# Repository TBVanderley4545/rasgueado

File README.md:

# Rasgueado

## Overview

Rasgueado - A strumming technique associated with flamenco music. Also, replacement controllers for Kinesis Advantage 2 boards.

This project was inspired by work from the [KinT project](https://github.com/kinx-project/kint) and the [Pillz Mod project](https://github.com/dcpedit/pillzmod).

The goal of this project was really simple, I wanted Nice!Nanos and ZMK in my Kinesis Advantage 2 boards. I wanted to make this PCB as simple as possible, so it is really barebones - no LEDs, no plans for batteries, just plain simple ZMK goodness. If I want to use my boards unplugged from my computer, I plug them into an external battery bank. I like this approach better because of super long battery life, easier modularity, and not needing to source tiny batteries.

In addition to the main controller, there are replacement thumb PCBs as well as plate files. Why? I wanted hotswap thumb clusters and carbon fiber plates. So, voila there are now hotswap thumb cluster PCBs and thumb plates that can be made in carbon fiber or whatever other material you please. Nice.

## Usage

You can find the zipped gerbers (for the pcb) and dxf file (for the plates) to send off for manufacturing or clone this repo and make whatever changes you want.

If you are working on the Kicad files, you will need to setup your Kicad to reference the following libraries:

- [ai03-2725 MX_V2 library](https://github.com/ai03-2725/MX_V2)
- [ScottoKicad library](https://github.com/joe-scotto/scottokeebs/tree/main/Extras/ScottoKicad)

## Parts lists

These parts lists are just based off of what I used and are here to help point you in the right direction. Feel free to buy from different places.

### Main Controller

| Part                                             | Qty | Notes                                                                                                                                                                                                                                                                                                                                                                                                                                                                          |
| ------------------------------------------------ | --- | ------------------------------------------------------------------------------------------------------------------------------------------------------------------------------------------------------------------------------------------------------------------------------------------------------------------------------------------------------------------------------------------------------------------------------------------------------------------------------ |
| Nice!Nano V2                                     | 1   | The MCU. The brains behind the board. [Link](https://typeractive.xyz/products/nice-nano?_pos=1&_sid=3e0c6f7de&_ss=r)                                                                                                                                                                                                                                                                                                                                                           |
| EZ-Solder Machine Sockets and Headers (optional) | 1   | These are optional, but they make socketing the Nice!Nano a breeze. I won't build without them personally. Your call though. [Link](https://typeractive.xyz/products/ez-machine-sockets-and-headers?_pos=3&_sid=3e0c6f7de&_ss=r)                                                                                                                                                                                                                                               |
| Molex 39-53-2135                                 | 6   | Connector for flat cables of other boards to plug into main board. [Link](https://www.digikey.com/en/products/detail/molex/0039532135/3160262)                                                                                                                                                                                                                                                                                                                                 |
| SN74HC595N Shift Register                        | 1   | Shift registers are cool. They make not enough GPIO pins into more than enough GPIO pins. Praise be to the shift registers. [Link](https://www.amazon.com/dp/B0CBKJXP13?ref_=ppx_hzsearch_conn_dt_b_fed_asin_title_1&th=1)                                                                                                                                                                                                                                                     |
| Shift Register Sockets                           | 1   | Sockets your shift register. Sweeeeeet. [Link](https://www.amazon.com/dp/B00SWO3U1C?ref_=ppx_hzsearch_conn_dt_b_fed_asin_title_2)                                                                                                                                                                                                                                                                                                                                              |
| USB C panel jack (optional)                      | 1   | This gives you a place to attach and detach USB C cables to the keyboard. Is this optional? Yes. It is indeed optional if you want to directly attach a USB C cable to your MCU and run the risk of damaging it and deal with never swapping out the cable easily. It is indeed optional. It's just a bad option not to. You live life on the edge. Installing this does require dremelling some material from your case though. [Link](https://www.adafruit.com/product/4218) |

### Thumbs

| Part                        | Qty | Notes                                                                                                                                                                                                                                                                                                               |
| --------------------------- | --- | ------------------------------------------------------------------------------------------------------------------------------------------------------------------------------------------------------------------------------------------------------------------------------------------------------------------- |
| Molex 39-53-2135            | 2   | Connector for flat cables of other boards to plug into main board. [Link](https://www.digikey.com/en/products/detail/molex/0039532135/3160262)                                                                                                                                                                      |
| Flat flex cables (optional) | 2   | These are just replacement flat cables. They were thinner and easier to work with than the stock ones. You can probably just reuse the stock cables, but I wanted to have extras. So... I did the sensible thing. I bought 30 "backups" [Link](https://www.digikey.com/en/products/detail/molex/0151680815/4143332) |
| 1N4148W SOD-123 diodes      | 12  | Diodes. They let signal go one way, but not the other. Without these there is only chaos. [Link](https://typeractive.xyz/products/smd-diodes?_pos=1&_sid=43b6f9089&_ss=r)                                                                                                                                           |
| Hotswap sockets             | 12  | Makes changing switches a breeze. That's hot. [Link](https://www.gateron.com/products/gateron-hot-swap-pcb-socket?VariantsId=10170)                                                                                                                                                                                 |
| Switches                    | 12  | 12 of whatever MX switches you want.                                                                                                                                                                                                                                                                                |

### Plates

They're reversible, so get two of them.

## Firmware

Link to the firmware repo [here](https://github.com/TBVanderley4545/zmk-config-rasgueado)

## Credits

- The MX footprint is from the [ai03-2725 MX_V2 library](https://github.com/ai03-2725/MX_V2)
- The 39-53-2135 footprint is from the [KinT project](https://github.com/kinx-project/kint)
- The Nice!Nano Footprint is from the [ScottoKicad library](https://github.com/joe-scotto/scottokeebs/tree/main/Extras/ScottoKicad)
- The SOD-123 Footprint is from the [ScottoKicad library](https://github.com/joe-scotto/scottokeebs/tree/main/Extras/ScottoKicad)

## Pictures

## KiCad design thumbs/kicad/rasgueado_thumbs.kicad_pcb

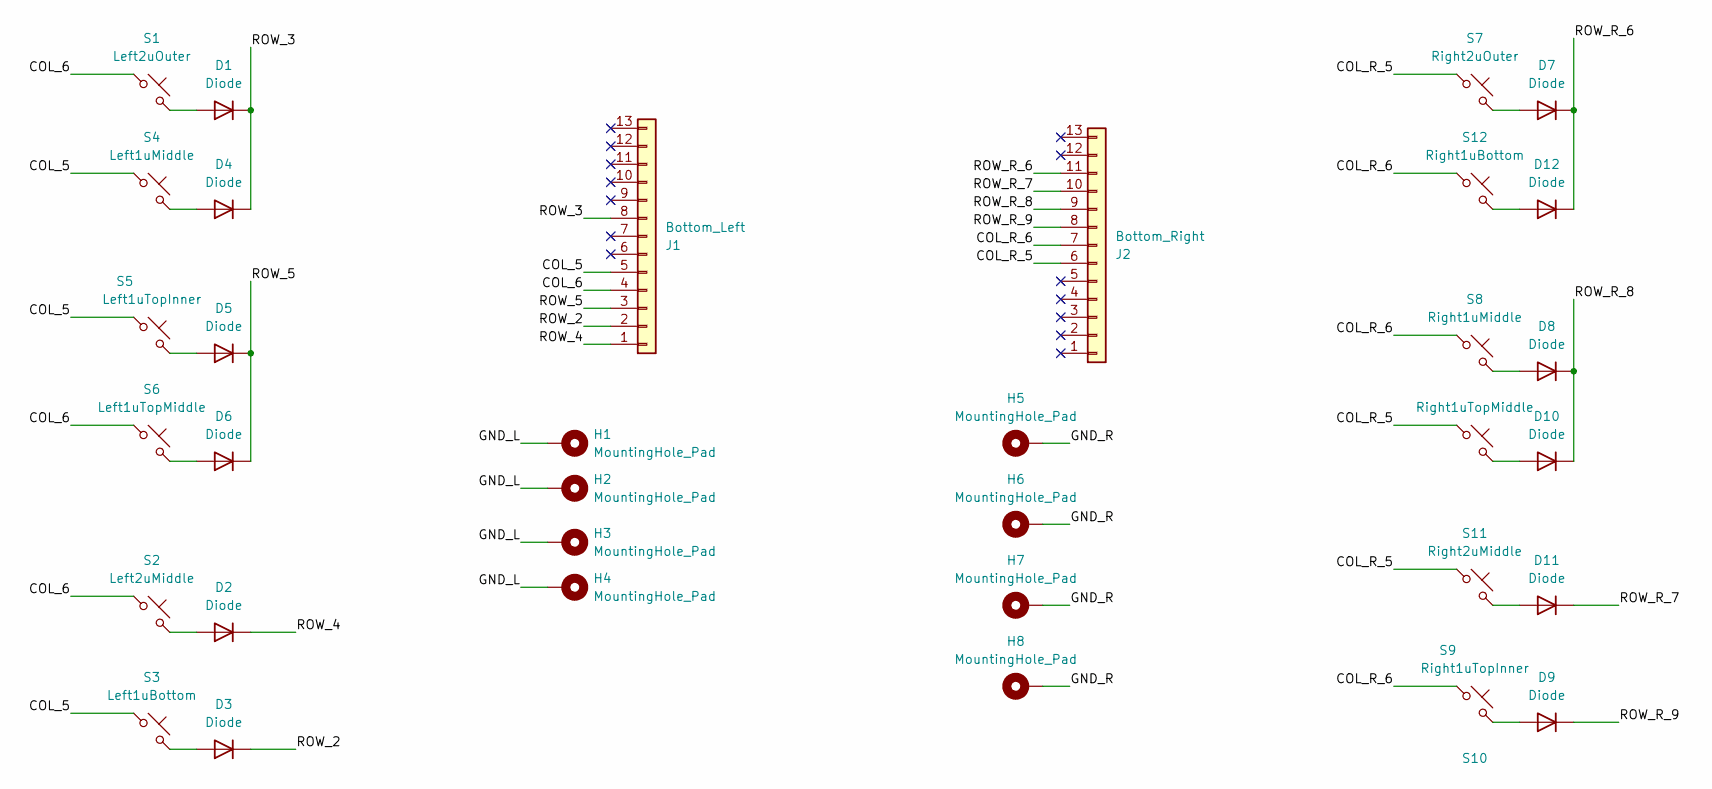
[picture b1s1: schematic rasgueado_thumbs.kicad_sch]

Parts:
D1, D2, D3, D4, D5, D6, D7, D8, D9, D10, D11, D12: Diode; Diode_SOD-123
H1, H2, H3, H4, H5, H6, H7, H8: MountingHole_Pad; MountingHole_3.7mm_Pad
J1: Bottom_Left; 39-53-2135
J2: Bottom_Right; 39-53-2135
S1: Left2uOuter; MX-Hotswap-1U
S2: Left2uMiddle; MX-Hotswap-1U
S3: Left1uBottom; MX-Hotswap-1U
S4: Left1uMiddle; MX-Hotswap-1U
S5: Left1uTopInner; MX-Hotswap-1U
S6: Left1uTopMiddle; MX-Hotswap-1U
S7: Right2uOuter; MX-Hotswap-1U
S8: Right1uMiddle; MX-Hotswap-1U
S9: Right1uTopInner; MX-Hotswap-1U
S10: Right1uTopMiddle; MX-Hotswap-1U
S11: Right2uMiddle; MX-Hotswap-1U
S12: Right1uBottom; MX-Hotswap-1U

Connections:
/COL_5: J1.5, S3.1, S4.1, S5.1
/COL_6: J1.4, S1.1, S2.1, S6.1
/COL_R_5: J2.6, S7.1, S10.1, S11.1
/COL_R_6: J2.7, S8.1, S9.1, S12.1
/GND_L: H1.1, H2.1, H3.1, H4.1
/GND_R: H5.1, H6.1, H7.1, H8.1
/ROW_2: D3.1 (K), J1.2
/ROW_3: D1.1 (K), D4.1 (K), J1.8
/ROW_4: D2.1 (K), J1.1
/ROW_5: D5.1 (K), D6.1 (K), J1.3
/ROW_R_6: D7.1 (K), D12.1 (K), J2.11
/ROW_R_7: D11.1 (K), J2.10
/ROW_R_8: D8.1 (K), D10.1 (K), J2.9
/ROW_R_9: D9.1 (K), J2.8
unnamed: D1.2 (A), S1.2
unnamed: D2.2 (A), S2.2
unnamed: D3.2 (A), S3.2
unnamed: D4.2 (A), S4.2
unnamed: D5.2 (A), S5.2
unnamed: D6.2 (A), S6.2
unnamed: D7.2 (A), S7.2
unnamed: D8.2 (A), S8.2
unnamed: D9.2 (A), S9.2
unnamed: D10.2 (A), S10.2
unnamed: D11.2 (A), S11.2
unnamed: D12.2 (A), S12.2

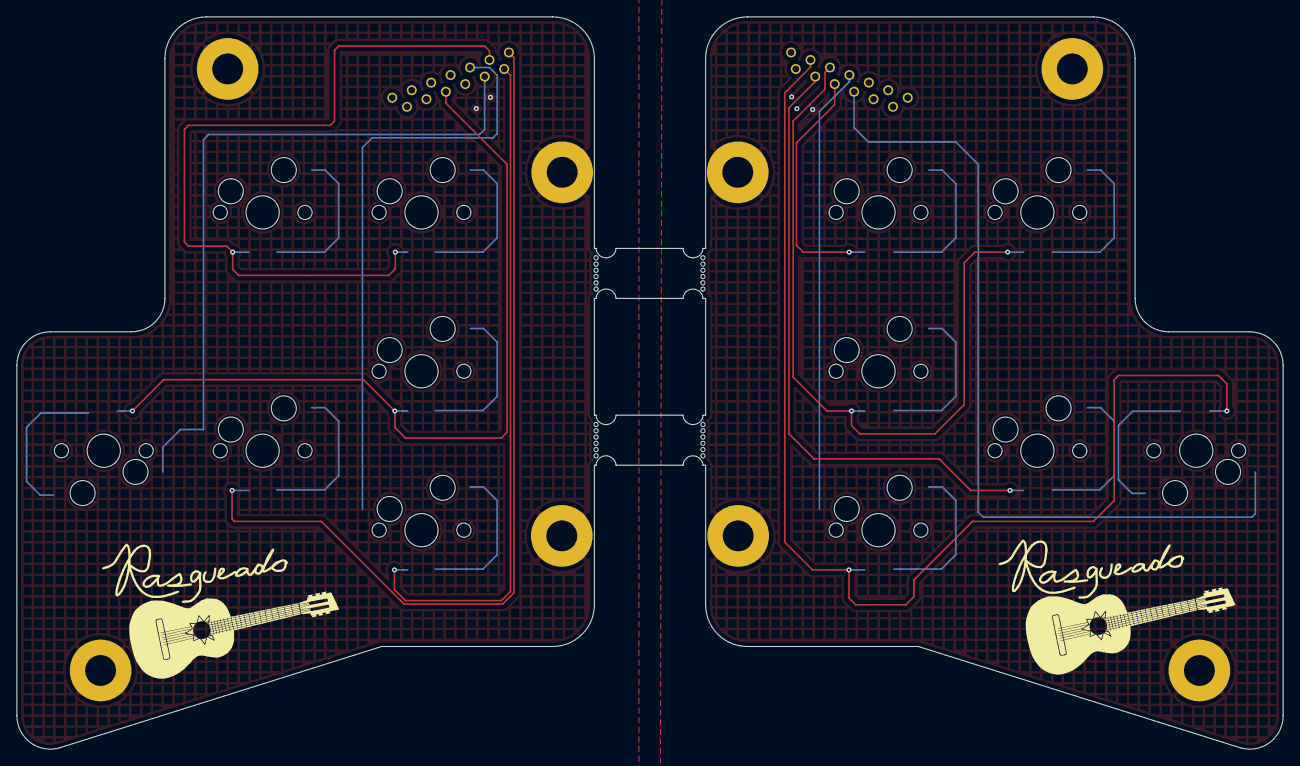
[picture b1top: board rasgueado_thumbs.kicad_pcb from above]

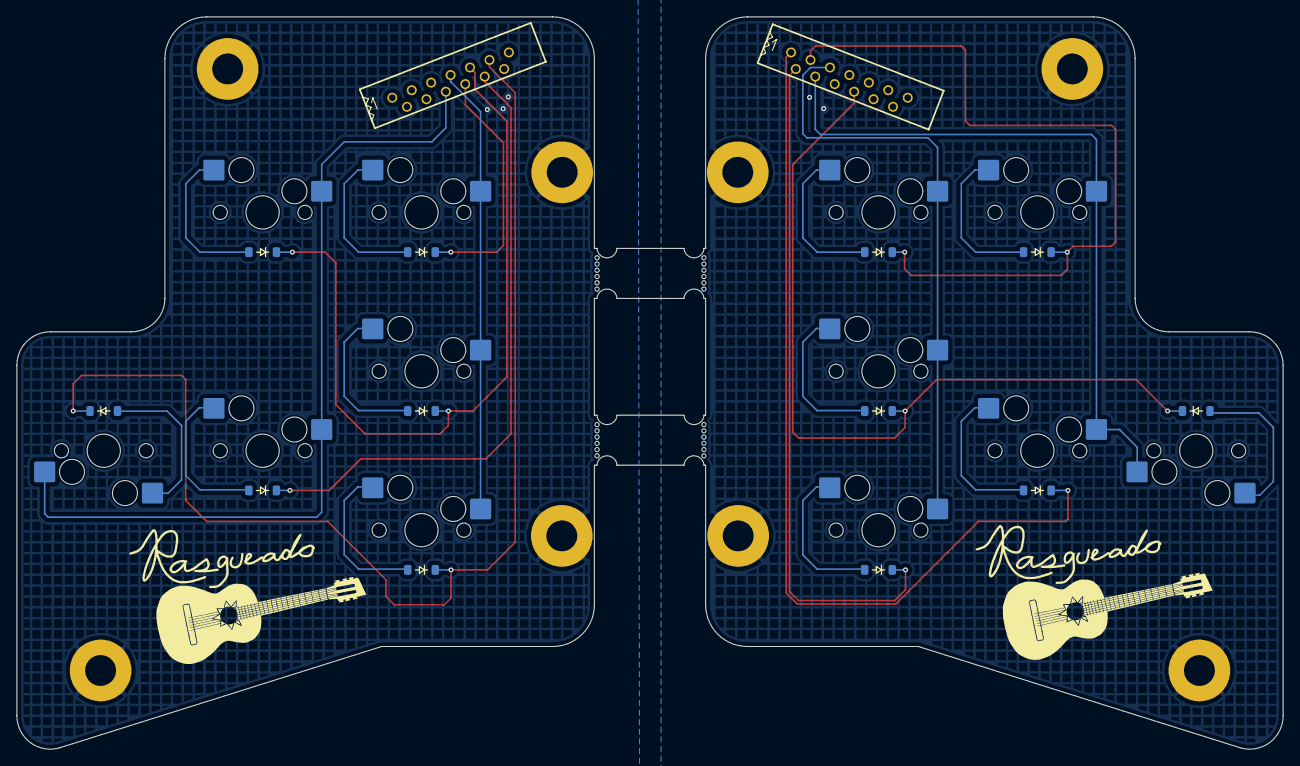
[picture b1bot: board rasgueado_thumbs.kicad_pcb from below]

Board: 2 copper layers, 151.8 x 87.8 mm, 34 parts (26 on the bottom side), 26 nets.

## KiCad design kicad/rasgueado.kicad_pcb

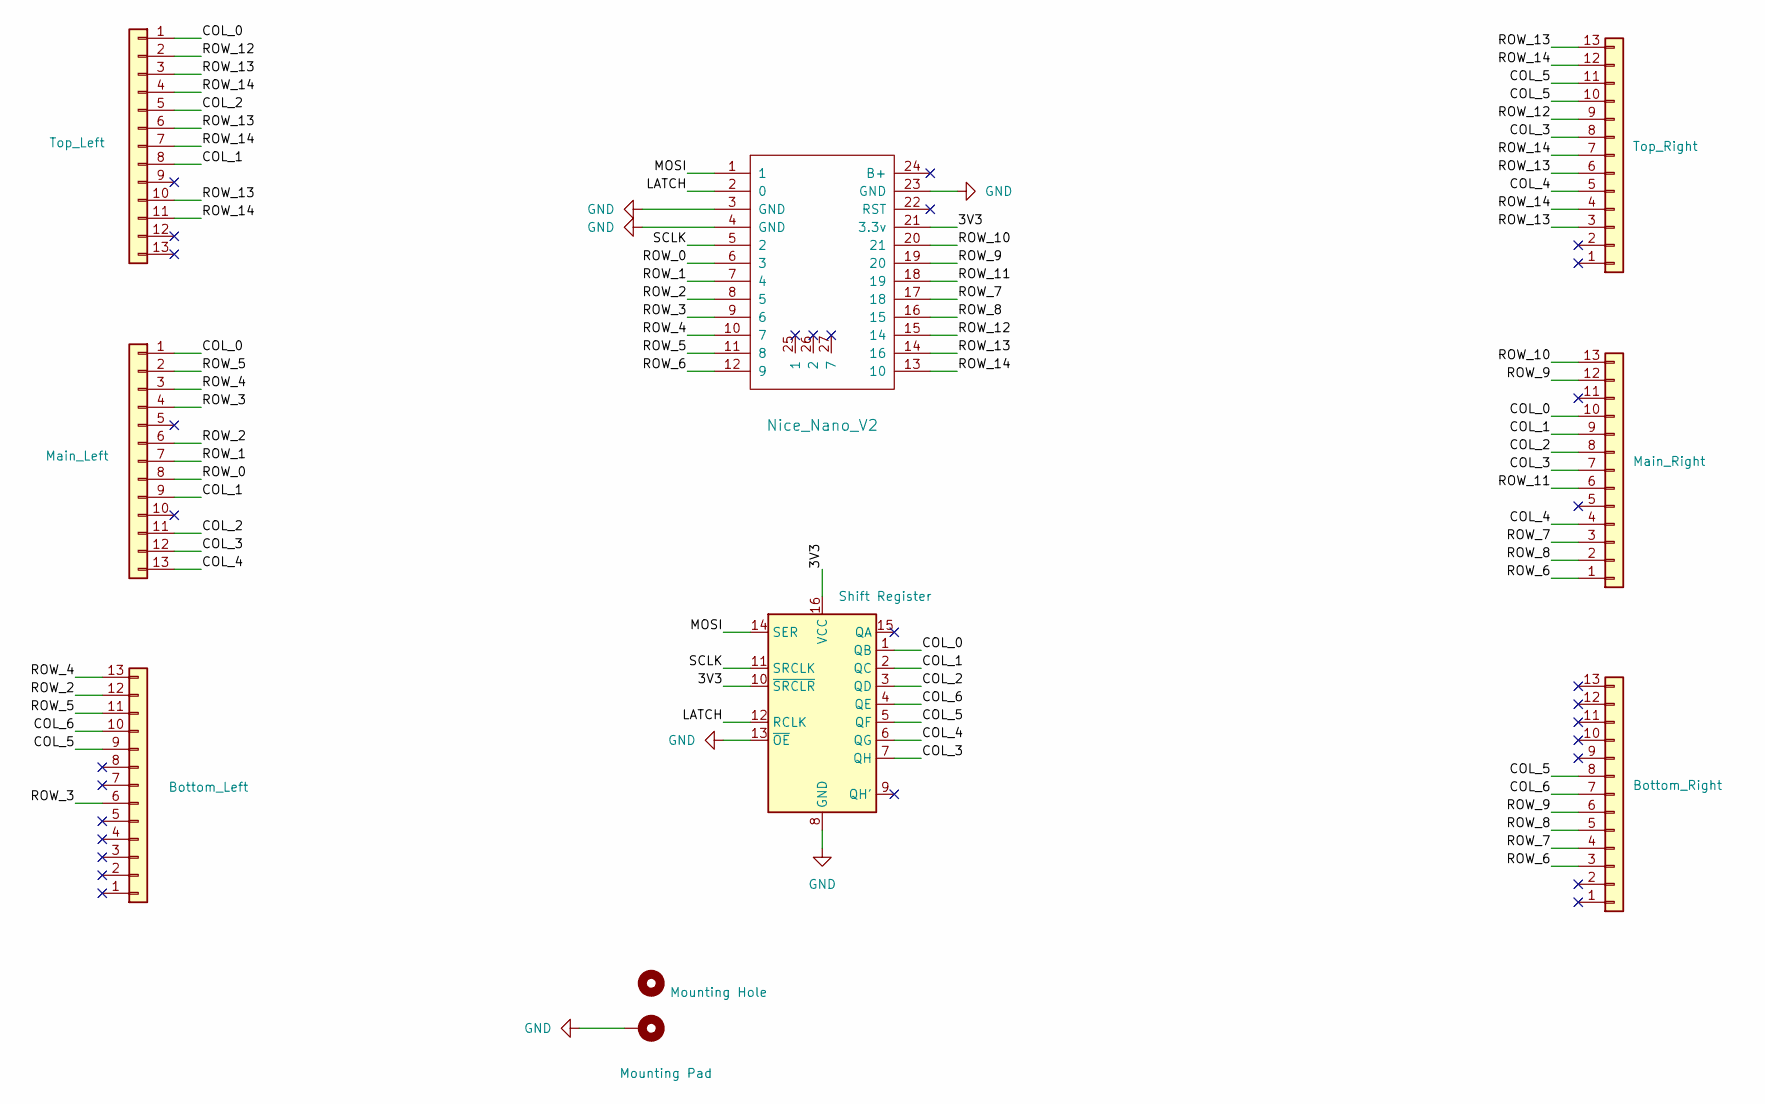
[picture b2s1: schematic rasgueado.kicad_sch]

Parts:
H1: Mounting Pad; MountingHole_4.3mm_M4_Pad
H2: Mounting Hole; MountingHole_6mm
J1: Top_Left; 39-53-2135
J2: Main_Left; 39-53-2135
J3: Bottom_Left; 39-53-2135
J4: Top_Right; 39-53-2135
J5: Main_Right; 39-53-2135
J6: Bottom_Right; 39-53-2135
U1: Nice_Nano_V2
U2: Shift Register; DIP-16_W7.62mm

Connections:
/3V3: U1.21 (3.3v), U2.10 (~SRCLR), U2.16 (VCC)
/COL_0: J1.1, J2.1, J5.10, U2.1 (QB)
/COL_1: J1.8, J2.9, J5.9, U2.2 (QC)
/COL_2: J1.5, J2.11, J5.8, U2.3 (QD)
/COL_3: J2.12, J4.8, J5.7, U2.7 (QH)
/COL_4: J2.13, J4.5, J5.4, U2.6 (QG)
/COL_5: J3.9, J4.10, J4.11, J6.8, U2.5 (QF)
/COL_6: J3.10, J6.7, U2.4 (QE)
/LATCH: U1.2 (0), U2.12 (RCLK)
/MOSI: U1.1, U2.14 (SER)
/ROW_0: J2.8, U1.6 (3)
/ROW_1: J2.7, U1.7 (4)
/ROW_2: J2.6, J3.12, U1.8 (5)
/ROW_3: J2.4, J3.6, U1.9 (6)
/ROW_4: J2.3, J3.13, U1.10 (7)
/ROW_5: J2.2, J3.11, U1.11 (8)
/ROW_6: J5.1, J6.3, U1.12 (9)
/ROW_7: J5.3, J6.4, U1.17 (18)
/ROW_8: J5.2, J6.5, U1.16 (15)
/ROW_9: J5.12, J6.6, U1.19 (20)
/ROW_10: J5.13, U1.20 (21)
/ROW_11: J5.6, U1.18 (19)
/ROW_12: J1.2, J4.9, U1.15 (14)
/ROW_13: J1.3, J1.6, J1.10, J4.3, J4.6, J4.13, U1.14 (16)
/ROW_14: J1.4, J1.7, J1.11, J4.4, J4.7, J4.12, U1.13 (10)
/SCLK: U1.5 (2), U2.11 (SRCLK)
GND: H1.1, U1.3 (GND), U1.4 (GND), U1.23 (GND), U2.8 (GND), U2.13 (~OE)

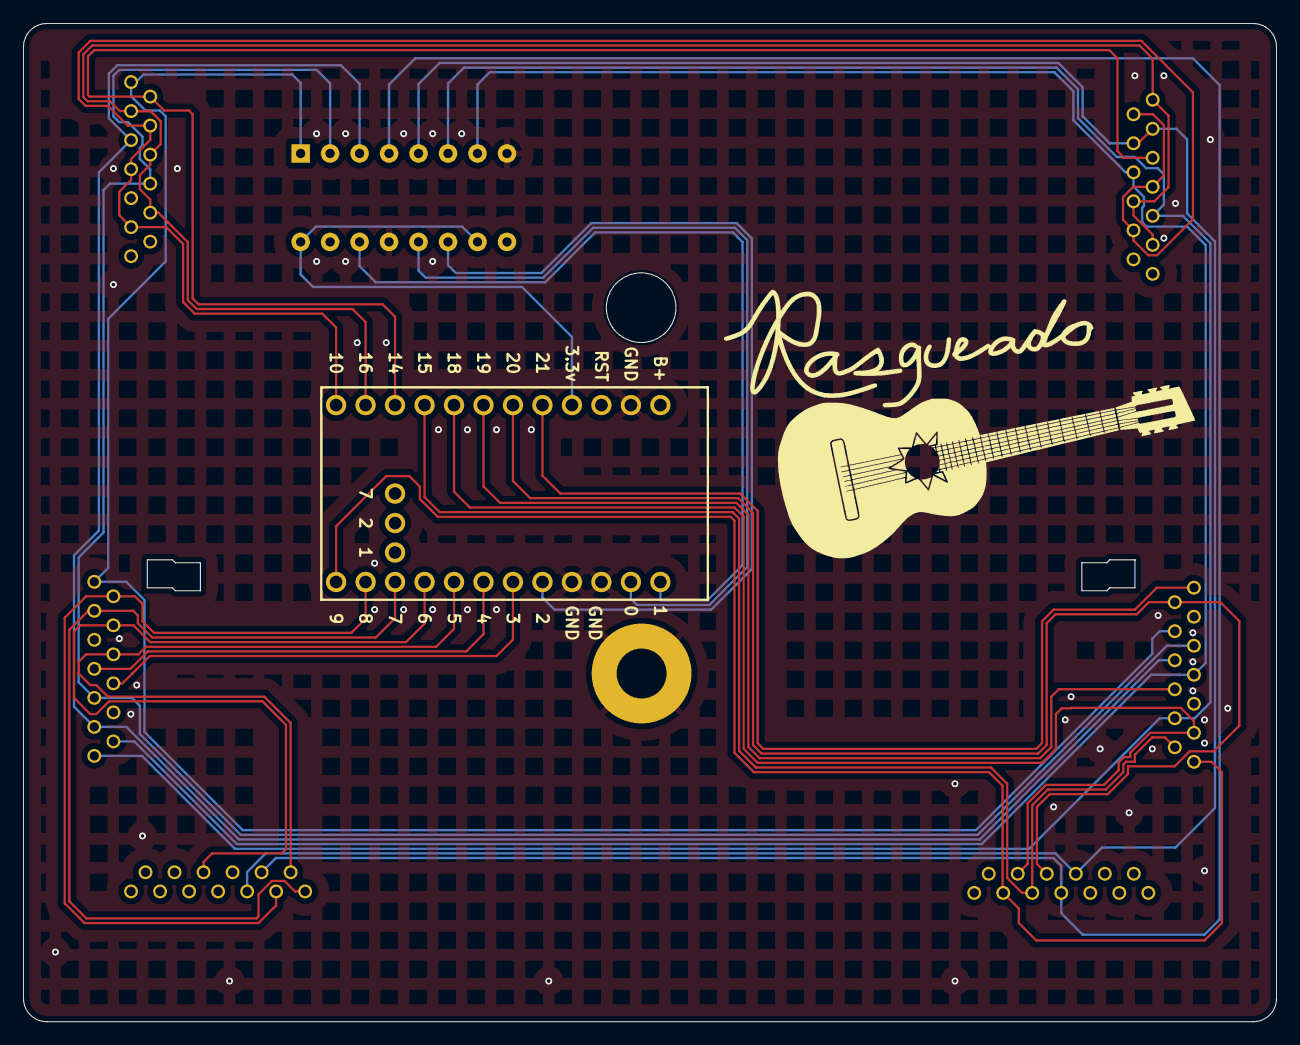
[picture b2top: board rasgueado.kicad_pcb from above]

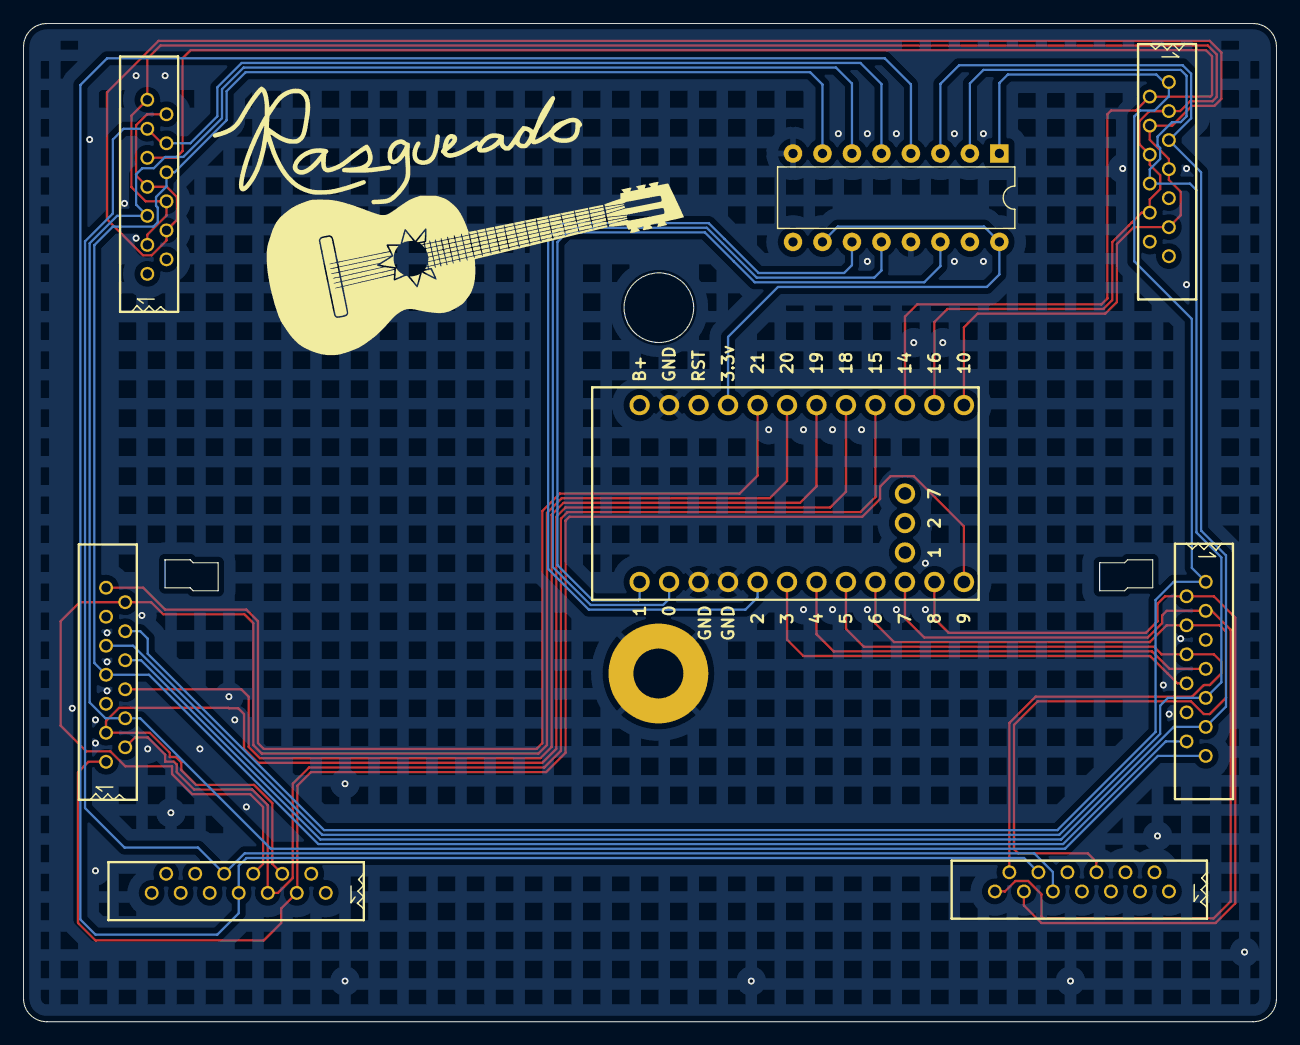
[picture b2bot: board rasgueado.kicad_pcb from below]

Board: 2 copper layers, 107.9 x 86.0 mm, 10 parts (8 on the bottom side), 27 nets.

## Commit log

2025-02-23 * Populate files from draft
